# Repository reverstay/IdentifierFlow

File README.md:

# **IdentifierFlow - Sistema de Controle de Acesso com Reconhecimento Facial**

## **Descrição do Projeto**
O **IdentifierFlow** é um sistema de controle de acesso baseado em **reconhecimento facial**, projetado para gerenciar entradas e saídas de pessoas em ambientes controlados, como academias, hospitais, empresas e órgãos públicos. O sistema integra **Flask, FastAPI, MQTT, ESP32, Flutter e Supabase** para oferecer um fluxo de autenticação seguro, automatizado e eficiente.

---

## **Arquitetura do Sistema**
O projeto é composto por diversos componentes que trabalham em conjunto para garantir o funcionamento adequado do sistema.  

### **1. ESP32 (Hardware - Catraca)**
- Conexão WiFi e MQTT para comunicação com o servidor.
- Processamento de comandos de liberação e negação de acesso.
- Controle de LEDs para indicar status de autenticação.
- Subscreve ao tópico MQTT para receber comandos do servidor.  

**Fluxograma:**
- Inicializa e conecta ao WiFi.
- Conecta ao broker MQTT.
- Processa comandos de liberação ("LIBERAR") ou negação ("NEGADO").
- Controla a catraca e exibe feedback visual via LEDs.

### **2. Backend (FastAPI + Flask)**
- Gerenciamento das solicitações de autenticação facial.
- Integração com a biblioteca `face_recognition` para identificação de usuários.
- API para envio de imagens de reconhecimento e sincronização de arquivos.
- Gerenciamento de usuários e permissões.

**Endpoints principais:**
- `/identify/` → Processa a imagem de um rosto e retorna permissão ou negação de acesso.
- `/sync-files/` → Sincroniza arquivos locais e remotos armazenados no **Supabase Storage**.

**Processo de Identificação:**
1. Baixa a imagem do usuário.
2. Processa e compara com o banco de dados.
3. Retorna um status (entrada/saída) e registra logs.

### **3. Aplicação Flutter (App do Usuário)**
- Interface móvel para usuários autenticarem a entrada via reconhecimento facial.
- Utiliza o **Google ML Kit** para detectar e capturar rostos.
- Faz upload das imagens para o **Supabase Storage**.
- Permite seleção de dispositivos de entrada e saída.

**Fluxo do App:**
1. Login do usuário.
2. Seleção do dispositivo (entrada/saída).
3. Captura de imagem via câmera do smartphone.
4. Upload da imagem para o servidor.
5. Retorno do status de acesso.

### **4. Painel Administrativo (Web)**
- Gerenciamento de usuários e permissões via interface web.
- Dashboards para administradores, diretores e recepcionistas.
- Controle de organizações e usuários (criação, edição e remoção).

**Funcionalidades principais:**
- Login e autenticação.
- Gerenciamento de organizações e diretores.
- Adição e remoção de recepcionistas e usuários.
- Visualização de logs de acesso.

---

## **Estrutura de Diretórios**
```
📂 CÓDIGOS  
│── 📂 __pycache__  
│── 📂 .vscode  
│── 📂 Catraca - ESP32 - C++    # Código do ESP32  
│── 📂 Flutter                 # Aplicação Flutter  
│── 📂 migrations              # Arquivos de migração do banco de dados  
│── 📂 static                  # Arquivos estáticos da aplicação web  
│── 📂 templates               # Templates HTML do painel administrativo  
│── 📂 usuarios                # Gerenciamento de usuários  
│── .env                       # Variáveis de ambiente  
│── app.py                     # Backend Flask  
│── fastAPI.py                 # Backend FastAPI  
│── fastAPI_funcional.py        # Funções auxiliares do FastAPI  
│── mqtt.py                     # Integração MQTT  
```

---

## **Tecnologias Utilizadas**
- **Backend:** Flask, FastAPI, Face Recognition  
- **Banco de Dados:** Supabase  
- **Frontend:** Flutter (mobile), HTML/CSS (web)  
- **Hardware:** ESP32 (WiFi + MQTT)  
- **Comunicação:** MQTT  

---

## **Configuração e Execução**

### **1. Clone este repositório:**
```bash
 git clone https://github.com/seu-repositorio.git
 cd IdentifierFlow
```

### **2. Instale as dependências do backend:**
```bash
pip install -r requirements.txt
```

### **3. Execute o backend Flask/FastAPI:**
```bash
python fastAPI.py
```

### **4. Suba o aplicativo Flutter:**
```bash
flutter run
```

### **5. Configure o ESP32:**
- Suba o firmware fornecido para o ESP32.
- Configure a conexão WiFi e MQTT.
- Certifique-se de que o dispositivo esteja conectado ao servidor corretamente.

---

## **Contribuição**
Caso queira contribuir com melhorias, faça um **fork** do repositório, crie uma **branch** e envie um **pull request** com suas sugestões.

---

## **Licença**
Este projeto está licenciado sob a **MIT License** - veja o arquivo [LICENSE](LICENSE) para mais detalhes.

---

Se precisar de ajustes ou adições, me avise! 🚀

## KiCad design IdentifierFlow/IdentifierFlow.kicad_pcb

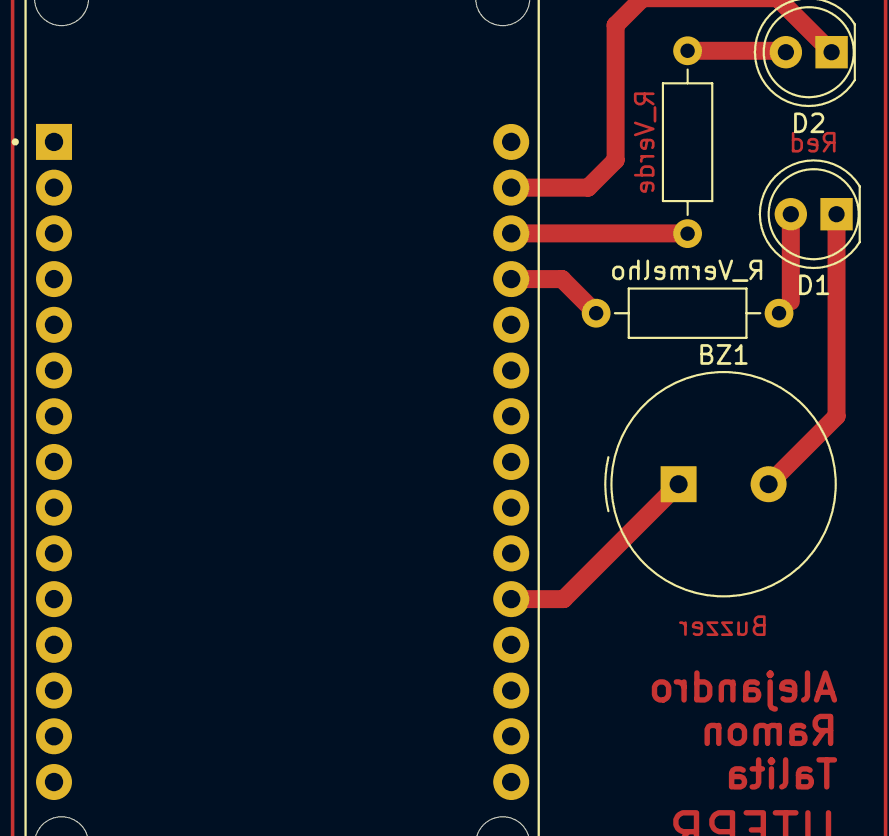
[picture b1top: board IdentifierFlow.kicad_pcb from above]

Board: 2 copper layers, 6 parts (0 on the bottom side), 6 nets.

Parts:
BZ1: Buzzer; Buzzer_TDK_PS1240P02BT_D12.2mm_H6.5mm
D1: Red; LED_D5.0mm
D2: Green; LED_D5.0mm
R_Verde: R; R_Axial_DIN0207_L6.3mm_D2.5mm_P10.16mm_Horizontal
R_Vermelho: R; R_Axial_DIN0207_L6.3mm_D2.5mm_P10.16mm_Horizontal
U1: ESP32-DEVKIT-V1; MODULE_ESP32_DEVKIT_V1

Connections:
GND: BZ1.2 (-), D1.1 (K), D2.1 (K), U1.2 (GND), U1.29 (GND)
unnamed: BZ1.1 (+), U1.20 (D35)
unnamed: D1.2 (A), R_Vermelho.2
unnamed: D2.2 (A), R_Verde.2
unnamed: R_Vermelho.1, U1.27 (D12)
unnamed: R_Verde.1, U1.28 (D13)

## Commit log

2024-11-07 Template Adicionado
2024-11-07 Docker adicionado
2024-12-02 aula do dia 02/12/2024
2025-02-16 Primeiro commit
2025-02-16 endpoint /identify/ excluido, nao estava sendo utilizado
2025-02-16 App flutter adicionado
2025-02-25 Update README.md
    descrição atualizada
